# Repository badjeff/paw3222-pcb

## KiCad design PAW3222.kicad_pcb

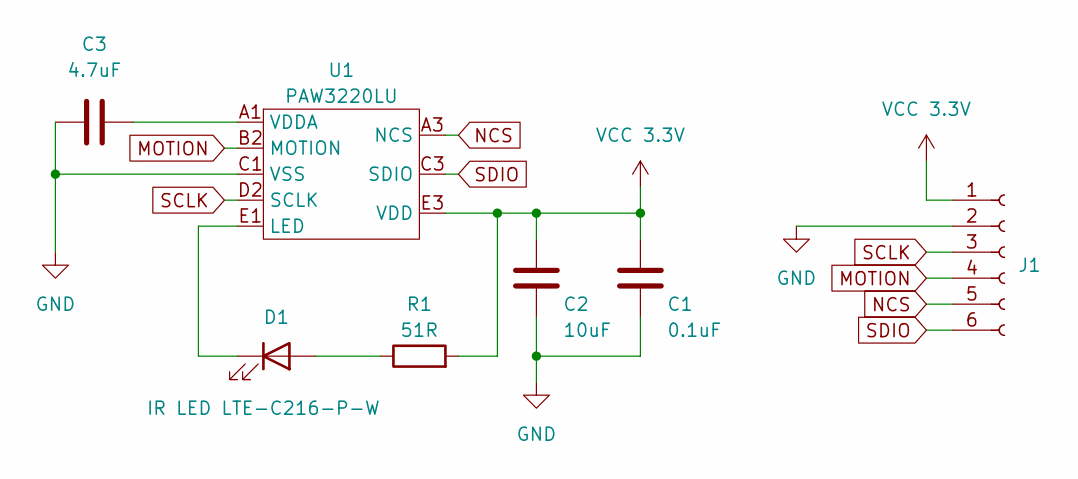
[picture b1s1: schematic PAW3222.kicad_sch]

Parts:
C1: 0.1uF; C_0402_1005Metric
C2: 10uF; C_0402_1005Metric
C3: 4.7uF; C_0402_1005Metric
D1: IR LED LTE-C216-P-W; LTE-C216-P-W; LCSC C2942980
J1: Conn_01x06_Socket; PinHeader_1x06_P1.27mm_Vertical
R1: 51R; R_0402_1005Metric
U1: PAW3220LU; PAW3222LU; LCSC C9900022540

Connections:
GND: C1.2, C2.2, C3.2, J1.2, U1.C1 (VSS)
MOTION: J1.4, U1.B2 (MOTION)
NCS: J1.5, U1.A3 (NCS)
unnamed: D1.2 (A), R1.1
unnamed: D1.1 (K), U1.E1 (LED)
unnamed: C3.1, U1.A1 (VDDA)
SCLK: J1.3, U1.D2 (SCLK)
SDIO: J1.6, U1.C3 (SDIO)
VCC 3.3V: C1.1, C2.1, J1.1, R1.2, U1.E3 (VDD)

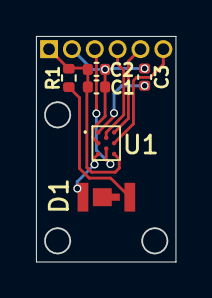
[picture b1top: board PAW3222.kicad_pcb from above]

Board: 2 copper layers, 7.7 x 12.5 mm, 7 parts (0 on the bottom side), 9 nets.

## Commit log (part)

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2025-11-01 init commit
